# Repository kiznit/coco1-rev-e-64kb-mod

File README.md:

# coco1-rev-e-64kb-mod
This project contains two breakout boards to upgrade a CoCo 1 Rev E from 32KB to 64KB without having to solder directly to U11 and U29.

- The first adapter for U29 (74LS02) has two PIN headers: one needs to be connected to **TP1** next to the CPU and the other to **U29** on U11's adapter.
- The second adapter for U11 (73LS138) has one PIN header that needs to be connected to **U11** on U29's adapter.

The **bin** folder contains zip files that can be uploaded directly to JLBPCB for production.

Update 2024/05/13:
I have assembled and tested the PCBs in my Rev E CoCo 1 and they work! I can now run 64 KB games like Sailor Man.

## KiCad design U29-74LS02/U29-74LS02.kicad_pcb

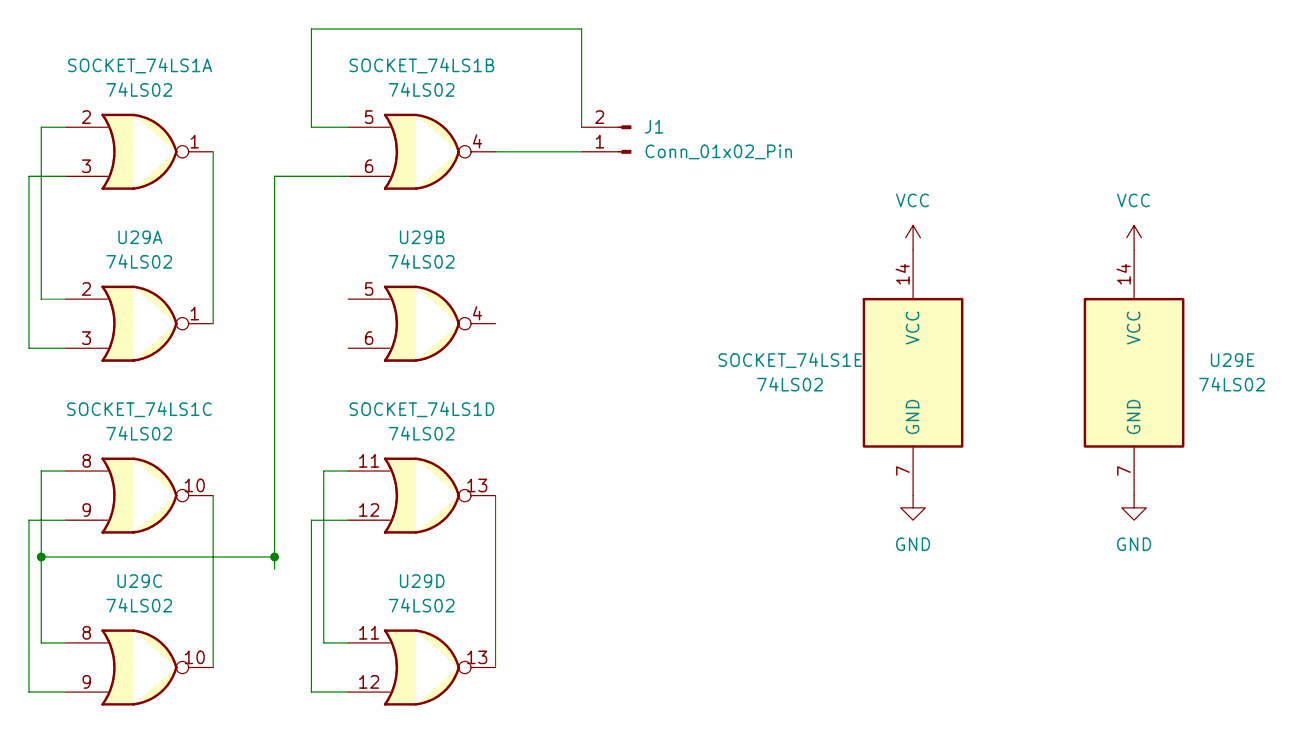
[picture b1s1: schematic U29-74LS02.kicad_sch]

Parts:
J1: Conn_01x02_Pin; PinHeader_1x02_P2.54mm_Vertical
SOCKET_74LS1: 74LS02; DIP-14_W7.62mm_Socket
U29: 74LS02; DIP-14_W7.62mm

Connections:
GND: SOCKET_74LS1.7 (GND), U29.7 (GND)
unnamed: J1.1, SOCKET_74LS1.4
unnamed: J1.2, SOCKET_74LS1.5
unnamed: SOCKET_74LS1.1, U29.1
unnamed: SOCKET_74LS1.2, U29.2
unnamed: SOCKET_74LS1.3, U29.3
unnamed: SOCKET_74LS1.6, SOCKET_74LS1.8, U29.8
unnamed: SOCKET_74LS1.9, U29.9
unnamed: SOCKET_74LS1.10, U29.10
unnamed: SOCKET_74LS1.11, U29.11
unnamed: SOCKET_74LS1.12, U29.12
unnamed: SOCKET_74LS1.13, U29.13
VCC: SOCKET_74LS1.14 (VCC), U29.14 (VCC)

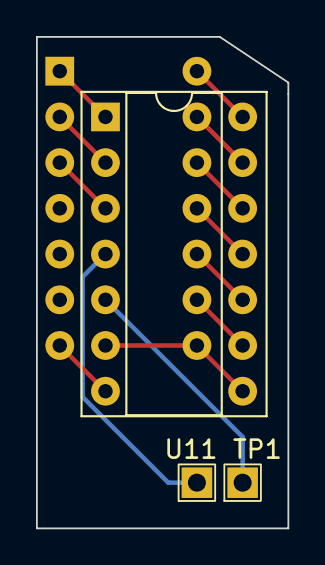
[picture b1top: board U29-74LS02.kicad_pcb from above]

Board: 2 copper layers, 14.0 x 27.3 mm, 3 parts (0 on the bottom side), 13 nets.

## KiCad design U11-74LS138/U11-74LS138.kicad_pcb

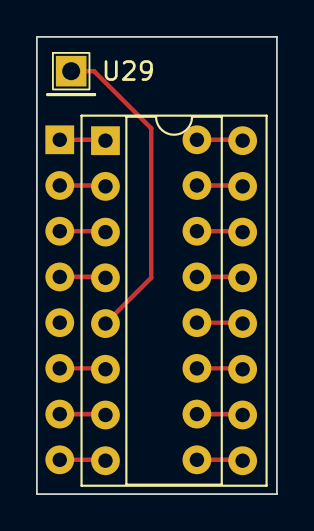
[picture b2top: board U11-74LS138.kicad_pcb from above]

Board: 2 copper layers, 13.3 x 25.4 mm, 3 parts (0 on the bottom side), 16 nets.

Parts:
SOCKET_74LS1: 74LS138; DIP-16_W7.62mm_Socket
U29: Conn_01x01_Pin; PinHeader_1x01_P2.54mm_Vertical
Ue: 74LS138; DIP-16_W7.62mm

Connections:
GND: SOCKET_74LS1.8 (GND), Ue.8 (GND)
unnamed: SOCKET_74LS1.5 (E2), U29.1
unnamed: SOCKET_74LS1.1 (A0), Ue.1 (A0)
unnamed: SOCKET_74LS1.2 (A1), Ue.2 (A1)
unnamed: SOCKET_74LS1.3 (A2), Ue.3 (A2)
unnamed: SOCKET_74LS1.4 (E1), Ue.4 (E1)
unnamed: SOCKET_74LS1.6 (E3), Ue.6 (E3)
unnamed: SOCKET_74LS1.15 (O0), Ue.15 (O0)
unnamed: SOCKET_74LS1.14 (O1), Ue.14 (O1)
unnamed: SOCKET_74LS1.13 (O2), Ue.13 (O2)
unnamed: SOCKET_74LS1.12 (O3), Ue.12 (O3)
unnamed: SOCKET_74LS1.11 (O4), Ue.11 (O4)
unnamed: SOCKET_74LS1.10 (O5), Ue.10 (O5)
unnamed: SOCKET_74LS1.9 (O6), Ue.9 (O6)
unnamed: SOCKET_74LS1.7 (O7), Ue.7 (O7)
VCC: SOCKET_74LS1.16 (VCC), Ue.16 (VCC)

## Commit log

2024-04-24 Initial revision.
2024-05-14 Add pictures.
